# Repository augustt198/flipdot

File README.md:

# flipdot

A driver board for my 16x28 flipdot display (Luminator MAX 3000).

The `connector` folder has a PCB for converting the 3x32 connector on the display to a
2x32 connector (which is easier to find cables for).

The `driver` folder has the driver board. Ideally I would like a footprint that fits both a teensy
and an ESP2866.

### Notes

- 15V is a good voltage to flip the dots, 50mA seems like enough current.

Front:

Back:

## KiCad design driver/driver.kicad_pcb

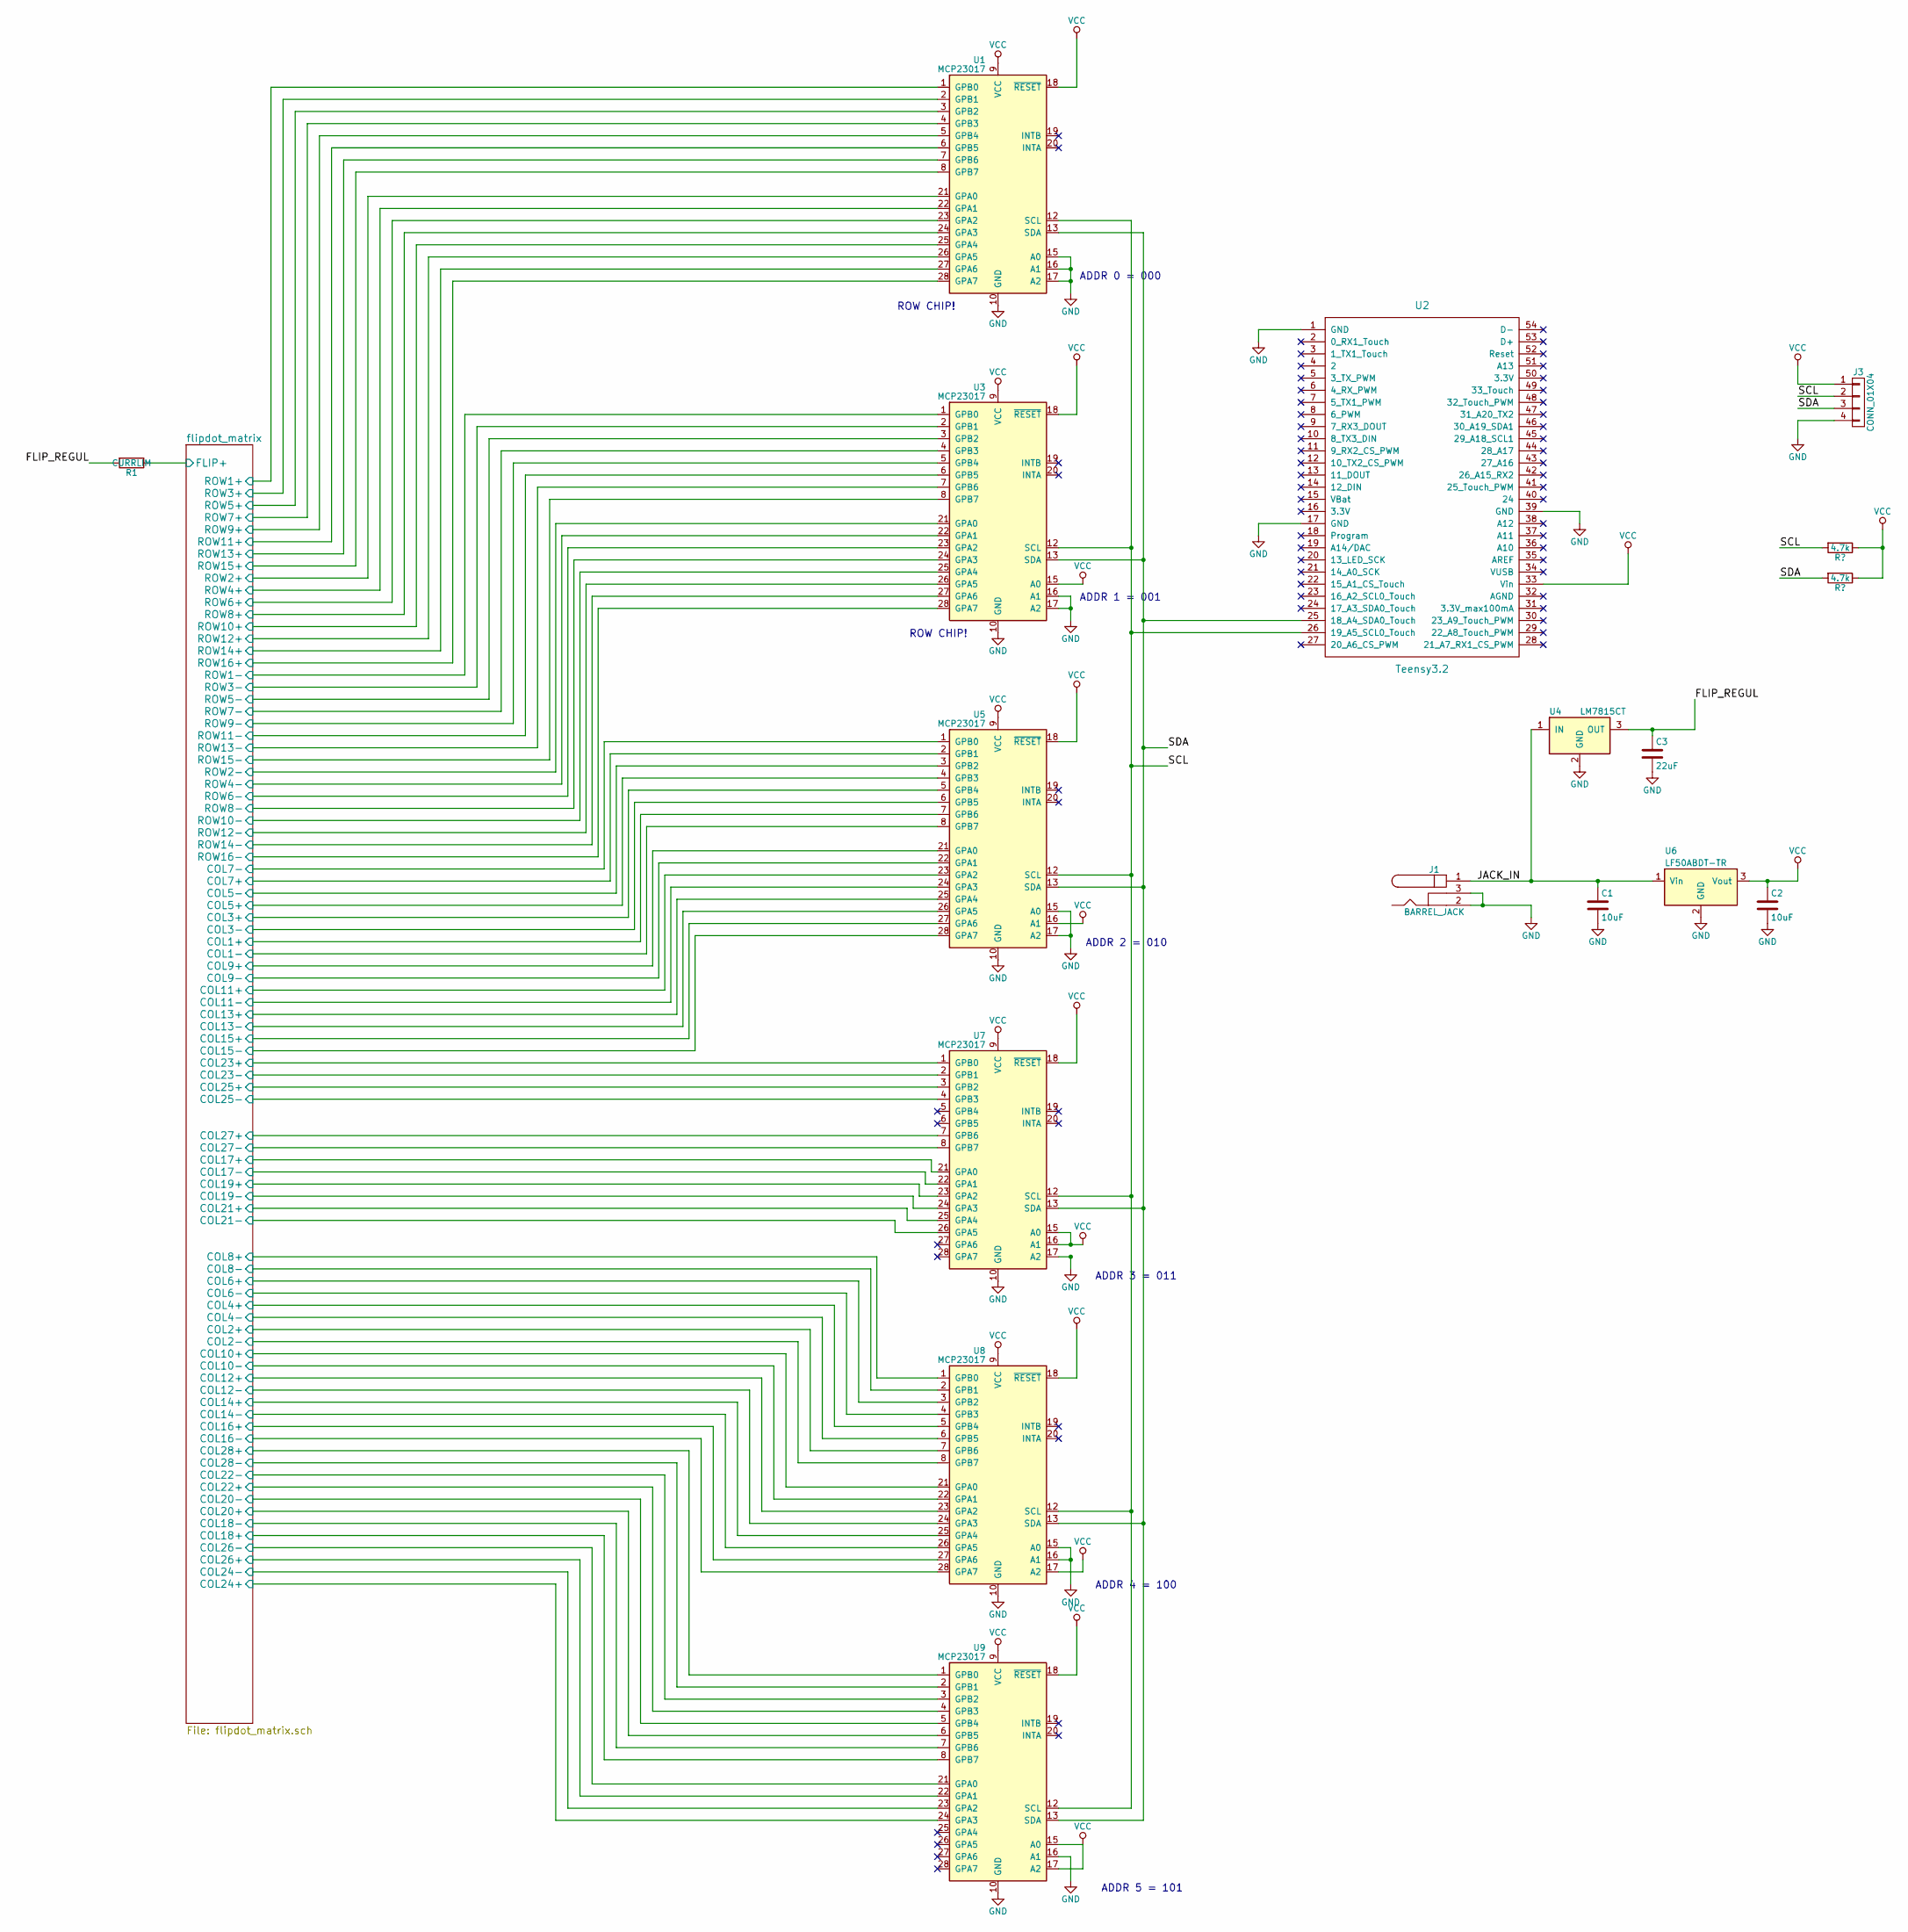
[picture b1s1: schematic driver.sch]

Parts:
C1, C2: 10uF; C_0805_HandSoldering
C3: 22uF; C_0805_HandSoldering
J1: BARREL_JACK
J3: CONN_01X04; Pin_Header_Straight_1x04_Pitch2.54mm
R1: CURRLIM; R_Axial_DIN0414_L11.9mm_D4.5mm_P15.24mm_Horizontal
U1, U3, U5, U7, U8, U9: MCP23017; SSOP-28_5.3x10.2mm_Pitch0.65mm
U2: Teensy3.2; Teensy30_31_32_LC
U4: LM7815CT; SOT-223-3Lead_TabPin2
U6: LF50ABDT-TR; SOT-223-3Lead_TabPin2

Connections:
/FLIP_REGUL: C3.1, R1.2, U4.3 (OUT)
/JACK_IN: C1.1, J1.1, U4.1 (IN), U6.1 (Vin)
/SCL: J3.2, U1.12 (SCL), U2.26 (19_A5_SCL0_Touch), U3.12 (SCL), U5.12 (SCL), U7.12 (SCL), U8.12 (SCL), U9.12 (SCL); also elsewhere on the board
/SDA: J3.3, U1.13 (SDA), U2.25 (18_A4_SDA0_Touch), U3.13 (SDA), U5.13 (SDA), U7.13 (SDA), U8.13 (SDA), U9.13 (SDA); also elsewhere on the board
/flipdot_matrix/COL1+: U5.7 (GPB6); also elsewhere on the board
/flipdot_matrix/COL1-: U5.8 (GPB7); also elsewhere on the board
/flipdot_matrix/COL2+: U8.7 (GPB6); also elsewhere on the board
/flipdot_matrix/COL2-: U8.8 (GPB7); also elsewhere on the board
/flipdot_matrix/COL3+: U5.5 (GPB4); also elsewhere on the board
/flipdot_matrix/COL3-: U5.6 (GPB5); also elsewhere on the board
/flipdot_matrix/COL4+: U8.5 (GPB4); also elsewhere on the board
/flipdot_matrix/COL4-: U8.6 (GPB5); also elsewhere on the board
/flipdot_matrix/COL5+: U5.4 (GPB3); also elsewhere on the board
/flipdot_matrix/COL5-: U5.3 (GPB2); also elsewhere on the board
/flipdot_matrix/COL6+: U8.3 (GPB2); also elsewhere on the board
/flipdot_matrix/COL6-: U8.4 (GPB3); also elsewhere on the board
/flipdot_matrix/COL7+: U5.2 (GPB1); also elsewhere on the board
/flipdot_matrix/COL7-: U5.1 (GPB0); also elsewhere on the board
/flipdot_matrix/COL8+: U8.1 (GPB0); also elsewhere on the board
/flipdot_matrix/COL8-: U8.2 (GPB1); also elsewhere on the board
/flipdot_matrix/COL9+: U5.21 (GPA0); also elsewhere on the board
/flipdot_matrix/COL9-: U5.22 (GPA1); also elsewhere on the board
/flipdot_matrix/COL10+: U8.21 (GPA0); also elsewhere on the board
/flipdot_matrix/COL10-: U8.22 (GPA1); also elsewhere on the board
/flipdot_matrix/COL11+: U5.23 (GPA2); also elsewhere on the board
/flipdot_matrix/COL11-: U5.24 (GPA3); also elsewhere on the board
/flipdot_matrix/COL12+: U8.23 (GPA2); also elsewhere on the board
/flipdot_matrix/COL12-: U8.24 (GPA3); also elsewhere on the board
/flipdot_matrix/COL13+: U5.25 (GPA4); also elsewhere on the board
/flipdot_matrix/COL13-: U5.26 (GPA5); also elsewhere on the board
/flipdot_matrix/COL14+: U8.25 (GPA4); also elsewhere on the board
/flipdot_matrix/COL14-: U8.26 (GPA5); also elsewhere on the board
/flipdot_matrix/COL15+: U5.27 (GPA6); also elsewhere on the board
/flipdot_matrix/COL15-: U5.28 (GPA7); also elsewhere on the board
/flipdot_matrix/COL16+: U8.27 (GPA6); also elsewhere on the board
/flipdot_matrix/COL16-: U8.28 (GPA7); also elsewhere on the board
/flipdot_matrix/COL17+: U7.21 (GPA0); also elsewhere on the board
/flipdot_matrix/COL17-: U7.22 (GPA1); also elsewhere on the board
/flipdot_matrix/COL18+: U9.8 (GPB7); also elsewhere on the board
/flipdot_matrix/COL18-: U9.7 (GPB6); also elsewhere on the board
/flipdot_matrix/COL19+: U7.23 (GPA2); also elsewhere on the board
/flipdot_matrix/COL19-: U7.24 (GPA3); also elsewhere on the board
/flipdot_matrix/COL20+: U9.6 (GPB5); also elsewhere on the board
/flipdot_matrix/COL20-: U9.5 (GPB4); also elsewhere on the board
/flipdot_matrix/COL21+: U7.25 (GPA4); also elsewhere on the board
/flipdot_matrix/COL21-: U7.26 (GPA5); also elsewhere on the board
/flipdot_matrix/COL22+: U9.4 (GPB3); also elsewhere on the board
/flipdot_matrix/COL22-: U9.3 (GPB2); also elsewhere on the board
/flipdot_matrix/COL23+: U7.1 (GPB0); also elsewhere on the board
/flipdot_matrix/COL23-: U7.2 (GPB1); also elsewhere on the board
/flipdot_matrix/COL24+: U9.24 (GPA3); also elsewhere on the board
/flipdot_matrix/COL24-: U9.23 (GPA2); also elsewhere on the board
/flipdot_matrix/COL25+: U7.3 (GPB2); also elsewhere on the board
/flipdot_matrix/COL25-: U7.4 (GPB3); also elsewhere on the board
/flipdot_matrix/COL26+: U9.22 (GPA1); also elsewhere on the board
/flipdot_matrix/COL26-: U9.21 (GPA0); also elsewhere on the board
/flipdot_matrix/COL27+: U7.7 (GPB6); also elsewhere on the board
/flipdot_matrix/COL27-: U7.8 (GPB7); also elsewhere on the board
/flipdot_matrix/COL28+: U9.1 (GPB0); also elsewhere on the board
/flipdot_matrix/COL28-: U9.2 (GPB1); also elsewhere on the board
/flipdot_matrix/FLIP+: R1.1; also elsewhere on the board
/flipdot_matrix/ROW1+: U1.2 (GPB1); also elsewhere on the board
/flipdot_matrix/ROW1-: U3.2 (GPB1); also elsewhere on the board
/flipdot_matrix/ROW2+: U1.22 (GPA1); also elsewhere on the board
/flipdot_matrix/ROW2-: U3.22 (GPA1); also elsewhere on the board
/flipdot_matrix/ROW3+: U1.1 (GPB0); also elsewhere on the board
/flipdot_matrix/ROW3-: U3.1 (GPB0); also elsewhere on the board
/flipdot_matrix/ROW4+: U1.21 (GPA0); also elsewhere on the board
/flipdot_matrix/ROW4-: U3.21 (GPA0); also elsewhere on the board
/flipdot_matrix/ROW5+: U1.4 (GPB3); also elsewhere on the board
/flipdot_matrix/ROW5-: U3.4 (GPB3); also elsewhere on the board
/flipdot_matrix/ROW6+: U1.24 (GPA3); also elsewhere on the board
/flipdot_matrix/ROW6-: U3.24 (GPA3); also elsewhere on the board
/flipdot_matrix/ROW7+: U1.3 (GPB2); also elsewhere on the board
/flipdot_matrix/ROW7-: U3.3 (GPB2); also elsewhere on the board
/flipdot_matrix/ROW8+: U1.23 (GPA2); also elsewhere on the board
/flipdot_matrix/ROW8-: U3.23 (GPA2); also elsewhere on the board
/flipdot_matrix/ROW9+: U1.6 (GPB5); also elsewhere on the board
/flipdot_matrix/ROW9-: U3.6 (GPB5); also elsewhere on the board
/flipdot_matrix/ROW10+: U1.26 (GPA5); also elsewhere on the board
/flipdot_matrix/ROW10-: U3.26 (GPA5); also elsewhere on the board
/flipdot_matrix/ROW11+: U1.5 (GPB4); also elsewhere on the board
/flipdot_matrix/ROW11-: U3.5 (GPB4); also elsewhere on the board
/flipdot_matrix/ROW12+: U1.25 (GPA4); also elsewhere on the board
/flipdot_matrix/ROW12-: U3.25 (GPA4); also elsewhere on the board
/flipdot_matrix/ROW13+: U1.8 (GPB7); also elsewhere on the board
/flipdot_matrix/ROW13-: U3.8 (GPB7); also elsewhere on the board
/flipdot_matrix/ROW14+: U1.28 (GPA7); also elsewhere on the board
/flipdot_matrix/ROW14-: U3.28 (GPA7); also elsewhere on the board
/flipdot_matrix/ROW15+: U1.7 (GPB6); also elsewhere on the board
/flipdot_matrix/ROW15-: U3.7 (GPB6); also elsewhere on the board
/flipdot_matrix/ROW16+: U1.27 (GPA6); also elsewhere on the board
/flipdot_matrix/ROW16-: U3.27 (GPA6); also elsewhere on the board
GND: C1.2, C2.2, C3.2, J1.2, J1.3, J3.4, U1.10 (GND), U1.15 (A0), U1.16 (A1), U1.17 (A2), U2.1 (GND), U2.17 (GND), U2.39 (GND), U3.10 (GND), U3.16 (A1), U3.17 (A2), U4.2 (GND), U5.10 (GND), U5.15 (A0), U5.17 (A2), U6.2 (GND), U7.10 (GND), U7.17 (A2), U8.10 (GND), U8.15 (A0), U8.16 (A1), U9.10 (GND), U9.16 (A1); also elsewhere on the board
VCC: C2.1, J3.1, U1.9 (VCC), U1.18 (~RESET), U2.33 (Vin), U3.9 (VCC), U3.15 (A0), U3.18 (~RESET), U5.9 (VCC), U5.16 (A1), U5.18 (~RESET), U6.3 (Vout), U7.9 (VCC), U7.15 (A0), U7.16 (A1), U7.18 (~RESET), U8.9 (VCC), U8.17 (A2), U8.18 (~RESET), U9.9 (VCC), U9.15 (A0), U9.17 (A2), U9.18 (~RESET); also elsewhere on the board

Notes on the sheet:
ADDR 0 = 000
ADDR 1 = 001
ADDR 2 = 010
ROW CHIP!
ADDR 3 = 011
ADDR 4 = 100
ADDR 5 = 101

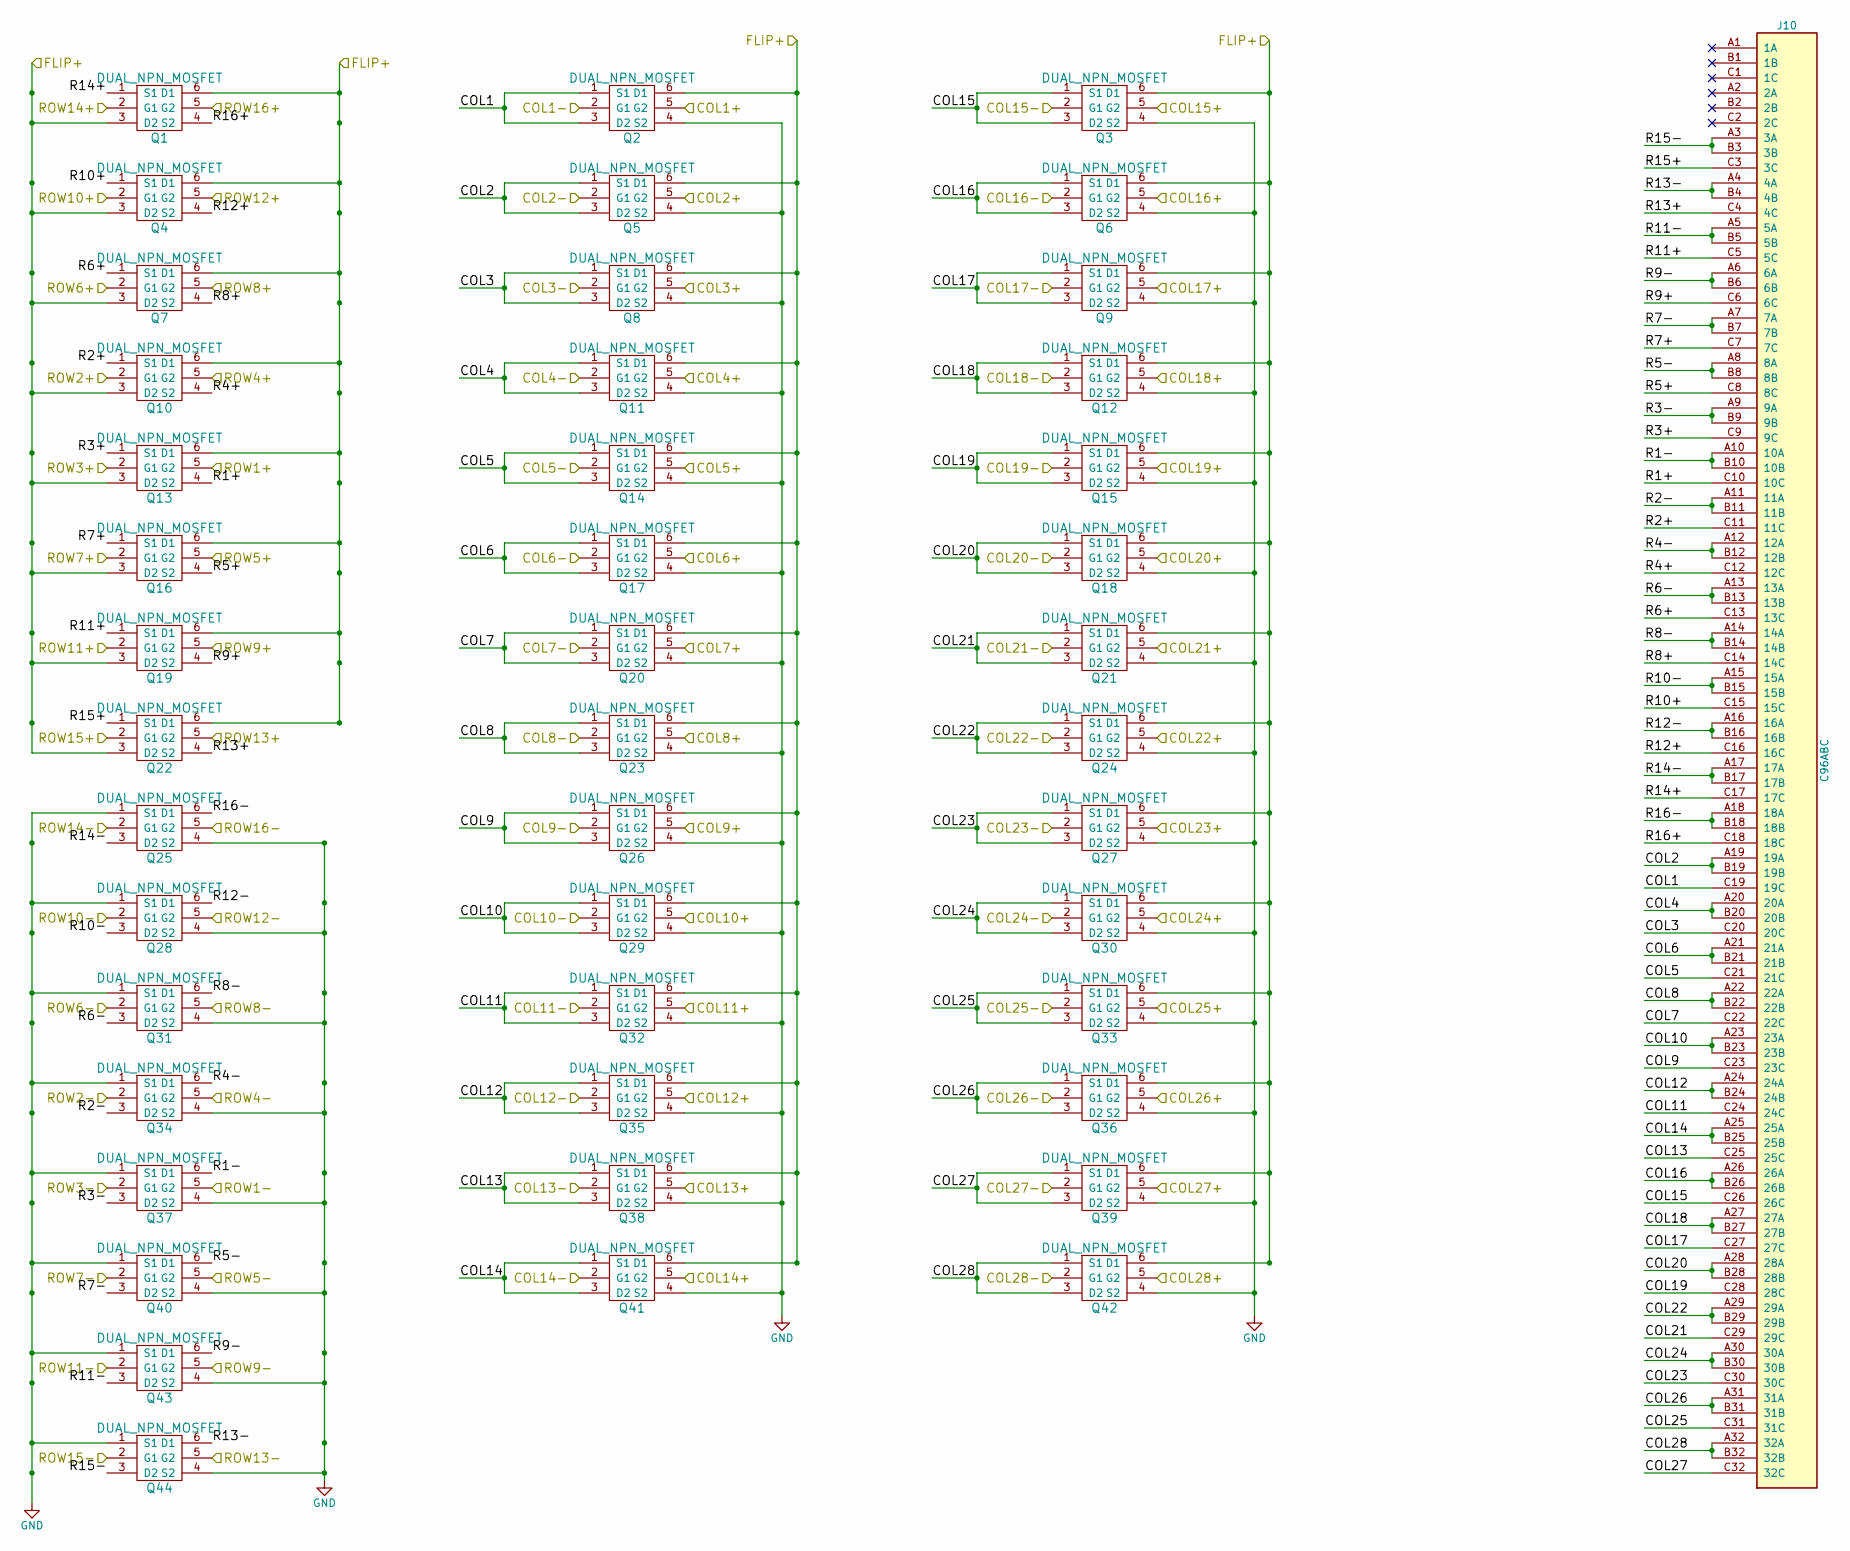
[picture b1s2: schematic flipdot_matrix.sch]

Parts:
J10: C96ABC; C96ABCMD_custom
Q1, Q2, Q3, Q4, Q5, Q6, Q7, Q8, Q9, Q10, Q11, Q12, Q13, Q14, Q15, Q16, Q17, Q18, Q19, Q20, Q21, Q22, Q23, Q24, Q25, Q26, Q27, Q28, Q29, Q30, Q31, Q32, Q33, Q34, Q35, Q36, Q37, Q38, Q39, Q40, Q41, Q42, Q43, Q44: DUAL_NPN_MOSFET; SOT-23-6_Handsoldering

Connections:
/flipdot_matrix/COL1: J10.C19 (19C), Q2.1 (S1), Q2.3 (D2)
/flipdot_matrix/COL1+: Q2.5 (G2); also elsewhere on the board
/flipdot_matrix/COL1-: Q2.2 (G1); also elsewhere on the board
/flipdot_matrix/COL2: J10.A19 (19A), J10.B19 (19B), Q5.1 (S1), Q5.3 (D2)
/flipdot_matrix/COL2+: Q5.5 (G2); also elsewhere on the board
/flipdot_matrix/COL2-: Q5.2 (G1); also elsewhere on the board
/flipdot_matrix/COL3: J10.C20 (20C), Q8.1 (S1), Q8.3 (D2)
/flipdot_matrix/COL3+: Q8.5 (G2); also elsewhere on the board
/flipdot_matrix/COL3-: Q8.2 (G1); also elsewhere on the board
/flipdot_matrix/COL4: J10.A20 (20A), J10.B20 (20B), Q11.1 (S1), Q11.3 (D2)
/flipdot_matrix/COL4+: Q11.5 (G2); also elsewhere on the board
/flipdot_matrix/COL4-: Q11.2 (G1); also elsewhere on the board
/flipdot_matrix/COL5: J10.C21 (21C), Q14.1 (S1), Q14.3 (D2)
/flipdot_matrix/COL5+: Q14.5 (G2); also elsewhere on the board
/flipdot_matrix/COL5-: Q14.2 (G1); also elsewhere on the board
/flipdot_matrix/COL6: J10.A21 (21A), J10.B21 (21B), Q17.1 (S1), Q17.3 (D2)
/flipdot_matrix/COL6+: Q17.5 (G2); also elsewhere on the board
/flipdot_matrix/COL6-: Q17.2 (G1); also elsewhere on the board
/flipdot_matrix/COL7: J10.C22 (22C), Q20.1 (S1), Q20.3 (D2)
/flipdot_matrix/COL7+: Q20.5 (G2); also elsewhere on the board
/flipdot_matrix/COL7-: Q20.2 (G1); also elsewhere on the board
/flipdot_matrix/COL8: J10.A22 (22A), J10.B22 (22B), Q23.1 (S1), Q23.3 (D2)
/flipdot_matrix/COL8+: Q23.5 (G2); also elsewhere on the board
/flipdot_matrix/COL8-: Q23.2 (G1); also elsewhere on the board
/flipdot_matrix/COL9: J10.C23 (23C), Q26.1 (S1), Q26.3 (D2)
/flipdot_matrix/COL9+: Q26.5 (G2); also elsewhere on the board
/flipdot_matrix/COL9-: Q26.2 (G1); also elsewhere on the board
/flipdot_matrix/COL10: J10.A23 (23A), J10.B23 (23B), Q29.1 (S1), Q29.3 (D2)
/flipdot_matrix/COL10+: Q29.5 (G2); also elsewhere on the board
/flipdot_matrix/COL10-: Q29.2 (G1); also elsewhere on the board
/flipdot_matrix/COL11: J10.C24 (24C), Q32.1 (S1), Q32.3 (D2)
/flipdot_matrix/COL11+: Q32.5 (G2); also elsewhere on the board
/flipdot_matrix/COL11-: Q32.2 (G1); also elsewhere on the board
/flipdot_matrix/COL12: J10.A24 (24A), J10.B24 (24B), Q35.1 (S1), Q35.3 (D2)
/flipdot_matrix/COL12+: Q35.5 (G2); also elsewhere on the board
/flipdot_matrix/COL12-: Q35.2 (G1); also elsewhere on the board
/flipdot_matrix/COL13: J10.C25 (25C), Q38.1 (S1), Q38.3 (D2)
/flipdot_matrix/COL13+: Q38.5 (G2); also elsewhere on the board
/flipdot_matrix/COL13-: Q38.2 (G1); also elsewhere on the board
/flipdot_matrix/COL14: J10.A25 (25A), J10.B25 (25B), Q41.1 (S1), Q41.3 (D2)
/flipdot_matrix/COL14+: Q41.5 (G2); also elsewhere on the board
/flipdot_matrix/COL14-: Q41.2 (G1); also elsewhere on the board
/flipdot_matrix/COL15: J10.C26 (26C), Q3.1 (S1), Q3.3 (D2)
/flipdot_matrix/COL15+: Q3.5 (G2); also elsewhere on the board
/flipdot_matrix/COL15-: Q3.2 (G1); also elsewhere on the board
/flipdot_matrix/COL16: J10.A26 (26A), J10.B26 (26B), Q6.1 (S1), Q6.3 (D2)
/flipdot_matrix/COL16+: Q6.5 (G2); also elsewhere on the board
/flipdot_matrix/COL16-: Q6.2 (G1); also elsewhere on the board
/flipdot_matrix/COL17: J10.C27 (27C), Q9.1 (S1), Q9.3 (D2)
/flipdot_matrix/COL17+: Q9.5 (G2); also elsewhere on the board
/flipdot_matrix/COL17-: Q9.2 (G1); also elsewhere on the board
/flipdot_matrix/COL18: J10.A27 (27A), J10.B27 (27B), Q12.1 (S1), Q12.3 (D2)
/flipdot_matrix/COL18+: Q12.5 (G2); also elsewhere on the board
/flipdot_matrix/COL18-: Q12.2 (G1); also elsewhere on the board
/flipdot_matrix/COL19: J10.C28 (28C), Q15.1 (S1), Q15.3 (D2)
/flipdot_matrix/COL19+: Q15.5 (G2); also elsewhere on the board
/flipdot_matrix/COL19-: Q15.2 (G1); also elsewhere on the board
/flipdot_matrix/COL20: J10.A28 (28A), J10.B28 (28B), Q18.1 (S1), Q18.3 (D2)
/flipdot_matrix/COL20+: Q18.5 (G2); also elsewhere on the board
/flipdot_matrix/COL20-: Q18.2 (G1); also elsewhere on the board
/flipdot_matrix/COL21: J10.C29 (29C), Q21.1 (S1), Q21.3 (D2)
/flipdot_matrix/COL21+: Q21.5 (G2); also elsewhere on the board
/flipdot_matrix/COL21-: Q21.2 (G1); also elsewhere on the board
/flipdot_matrix/COL22: J10.A29 (29A), J10.B29 (29B), Q24.1 (S1), Q24.3 (D2)
/flipdot_matrix/COL22+: Q24.5 (G2); also elsewhere on the board
/flipdot_matrix/COL22-: Q24.2 (G1); also elsewhere on the board
/flipdot_matrix/COL23: J10.C30 (30C), Q27.1 (S1), Q27.3 (D2)
/flipdot_matrix/COL23+: Q27.5 (G2); also elsewhere on the board
/flipdot_matrix/COL23-: Q27.2 (G1); also elsewhere on the board
/flipdot_matrix/COL24: J10.A30 (30A), J10.B30 (30B), Q30.1 (S1), Q30.3 (D2)
/flipdot_matrix/COL24+: Q30.5 (G2); also elsewhere on the board
/flipdot_matrix/COL24-: Q30.2 (G1); also elsewhere on the board
/flipdot_matrix/COL25: J10.C31 (31C), Q33.1 (S1), Q33.3 (D2)
/flipdot_matrix/COL25+: Q33.5 (G2); also elsewhere on the board
/flipdot_matrix/COL25-: Q33.2 (G1); also elsewhere on the board
/flipdot_matrix/COL26: J10.A31 (31A), J10.B31 (31B), Q36.1 (S1), Q36.3 (D2)
/flipdot_matrix/COL26+: Q36.5 (G2); also elsewhere on the board
/flipdot_matrix/COL26-: Q36.2 (G1); also elsewhere on the board
/flipdot_matrix/COL27: J10.C32 (32C), Q39.1 (S1), Q39.3 (D2)
/flipdot_matrix/COL27+: Q39.5 (G2); also elsewhere on the board
/flipdot_matrix/COL27-: Q39.2 (G1); also elsewhere on the board
/flipdot_matrix/COL28: J10.A32 (32A), J10.B32 (32B), Q42.1 (S1), Q42.3 (D2)
/flipdot_matrix/COL28+: Q42.5 (G2); also elsewhere on the board
/flipdot_matrix/COL28-: Q42.2 (G1); also elsewhere on the board
/flipdot_matrix/FLIP+: Q1.3 (D2), Q1.6 (D1), Q2.6 (D1), Q3.6 (D1), Q4.3 (D2), Q4.6 (D1), Q5.6 (D1), Q6.6 (D1), Q7.3 (D2), Q7.6 (D1), Q8.6 (D1), Q9.6 (D1), Q10.3 (D2), Q10.6 (D1), Q11.6 (D1), Q12.6 (D1), Q13.3 (D2), Q13.6 (D1), Q14.6 (D1), Q15.6 (D1), Q16.3 (D2), Q16.6 (D1), Q17.6 (D1), Q18.6 (D1), Q19.3 (D2), Q19.6 (D1), Q20.6 (D1), Q21.6 (D1), Q22.3 (D2), Q22.6 (D1), Q23.6 (D1), Q24.6 (D1), Q26.6 (D1), Q27.6 (D1), Q29.6 (D1), Q30.6 (D1), Q32.6 (D1), Q33.6 (D1), Q35.6 (D1), Q36.6 (D1), Q38.6 (D1), Q39.6 (D1), Q41.6 (D1), Q42.6 (D1); also elsewhere on the board
/flipdot_matrix/R1+: J10.C10 (10C), Q13.4 (S2)
/flipdot_matrix/R1-: J10.A10 (10A), J10.B10 (10B), Q37.6 (D1)
/flipdot_matrix/R2+: J10.C11 (11C), Q10.1 (S1)
/flipdot_matrix/R2-: J10.A11 (11A), J10.B11 (11B), Q34.3 (D2)
/flipdot_matrix/R3+: J10.C9 (9C), Q13.1 (S1)
/flipdot_matrix/R3-: J10.A9 (9A), J10.B9 (9B), Q37.3 (D2)
/flipdot_matrix/R4+: J10.C12 (12C), Q10.4 (S2)
/flipdot_matrix/R4-: J10.A12 (12A), J10.B12 (12B), Q34.6 (D1)
/flipdot_matrix/R5+: J10.C8 (8C), Q16.4 (S2)
/flipdot_matrix/R5-: J10.A8 (8A), J10.B8 (8B), Q40.6 (D1)
/flipdot_matrix/R6+: J10.C13 (13C), Q7.1 (S1)
/flipdot_matrix/R6-: J10.A13 (13A), J10.B13 (13B), Q31.3 (D2)
/flipdot_matrix/R7+: J10.C7 (7C), Q16.1 (S1)
/flipdot_matrix/R7-: J10.A7 (7A), J10.B7 (7B), Q40.3 (D2)
/flipdot_matrix/R8+: J10.C14 (14C), Q7.4 (S2)
/flipdot_matrix/R8-: J10.A14 (14A), J10.B14 (14B), Q31.6 (D1)
/flipdot_matrix/R9+: J10.C6 (6C), Q19.4 (S2)
/flipdot_matrix/R9-: J10.A6 (6A), J10.B6 (6B), Q43.6 (D1)
/flipdot_matrix/R10+: J10.C15 (15C), Q4.1 (S1)
/flipdot_matrix/R10-: J10.A15 (15A), J10.B15 (15B), Q28.3 (D2)
/flipdot_matrix/R11+: J10.C5 (5C), Q19.1 (S1)
/flipdot_matrix/R11-: J10.A5 (5A), J10.B5 (5B), Q43.3 (D2)
/flipdot_matrix/R12+: J10.C16 (16C), Q4.4 (S2)
/flipdot_matrix/R12-: J10.A16 (16A), J10.B16 (16B), Q28.6 (D1)
/flipdot_matrix/R13+: J10.C4 (4C), Q22.4 (S2)
/flipdot_matrix/R13-: J10.A4 (4A), J10.B4 (4B), Q44.6 (D1)
/flipdot_matrix/R14+: J10.C17 (17C), Q1.1 (S1)
/flipdot_matrix/R14-: J10.A17 (17A), J10.B17 (17B), Q25.3 (D2)
/flipdot_matrix/R15+: J10.C3 (3C), Q22.1 (S1)
/flipdot_matrix/R15-: J10.A3 (3A), J10.B3 (3B), Q44.3 (D2)
/flipdot_matrix/R16+: J10.C18 (18C), Q1.4 (S2)
/flipdot_matrix/R16-: J10.A18 (18A), J10.B18 (18B), Q25.6 (D1)
/flipdot_matrix/ROW1+: Q13.5 (G2); also elsewhere on the board
/flipdot_matrix/ROW1-: Q37.5 (G2); also elsewhere on the board
/flipdot_matrix/ROW2+: Q10.2 (G1); also elsewhere on the board
/flipdot_matrix/ROW2-: Q34.2 (G1); also elsewhere on the board
/flipdot_matrix/ROW3+: Q13.2 (G1); also elsewhere on the board
/flipdot_matrix/ROW3-: Q37.2 (G1); also elsewhere on the board
/flipdot_matrix/ROW4+: Q10.5 (G2); also elsewhere on the board
/flipdot_matrix/ROW4-: Q34.5 (G2); also elsewhere on the board
/flipdot_matrix/ROW5+: Q16.5 (G2); also elsewhere on the board
/flipdot_matrix/ROW5-: Q40.5 (G2); also elsewhere on the board
/flipdot_matrix/ROW6+: Q7.2 (G1); also elsewhere on the board
/flipdot_matrix/ROW6-: Q31.2 (G1); also elsewhere on the board
/flipdot_matrix/ROW7+: Q16.2 (G1); also elsewhere on the board
/flipdot_matrix/ROW7-: Q40.2 (G1); also elsewhere on the board
/flipdot_matrix/ROW8+: Q7.5 (G2); also elsewhere on the board
/flipdot_matrix/ROW8-: Q31.5 (G2); also elsewhere on the board
/flipdot_matrix/ROW9+: Q19.5 (G2); also elsewhere on the board
/flipdot_matrix/ROW9-: Q43.5 (G2); also elsewhere on the board
/flipdot_matrix/ROW10+: Q4.2 (G1); also elsewhere on the board
/flipdot_matrix/ROW10-: Q28.2 (G1); also elsewhere on the board
/flipdot_matrix/ROW11+: Q19.2 (G1); also elsewhere on the board
/flipdot_matrix/ROW11-: Q43.2 (G1); also elsewhere on the board
/flipdot_matrix/ROW12+: Q4.5 (G2); also elsewhere on the board
/flipdot_matrix/ROW12-: Q28.5 (G2); also elsewhere on the board
/flipdot_matrix/ROW13+: Q22.5 (G2); also elsewhere on the board
/flipdot_matrix/ROW13-: Q44.5 (G2); also elsewhere on the board
/flipdot_matrix/ROW14+: Q1.2 (G1); also elsewhere on the board
/flipdot_matrix/ROW14-: Q25.2 (G1); also elsewhere on the board
/flipdot_matrix/ROW15+: Q22.2 (G1); also elsewhere on the board
/flipdot_matrix/ROW15-: Q44.2 (G1); also elsewhere on the board
/flipdot_matrix/ROW16+: Q1.5 (G2); also elsewhere on the board
/flipdot_matrix/ROW16-: Q25.5 (G2); also elsewhere on the board
GND: Q2.4 (S2), Q3.4 (S2), Q5.4 (S2), Q6.4 (S2), Q8.4 (S2), Q9.4 (S2), Q11.4 (S2), Q12.4 (S2), Q14.4 (S2), Q15.4 (S2), Q17.4 (S2), Q18.4 (S2), Q20.4 (S2), Q21.4 (S2), Q23.4 (S2), Q24.4 (S2), Q25.1 (S1), Q25.4 (S2), Q26.4 (S2), Q27.4 (S2), Q28.1 (S1), Q28.4 (S2), Q29.4 (S2), Q30.4 (S2), Q31.1 (S1), Q31.4 (S2), Q32.4 (S2), Q33.4 (S2), Q34.1 (S1), Q34.4 (S2), Q35.4 (S2), Q36.4 (S2), Q37.1 (S1), Q37.4 (S2), Q38.4 (S2), Q39.4 (S2), Q40.1 (S1), Q40.4 (S2), Q41.4 (S2), Q42.4 (S2), Q43.1 (S1), Q43.4 (S2), Q44.1 (S1), Q44.4 (S2); also elsewhere on the board

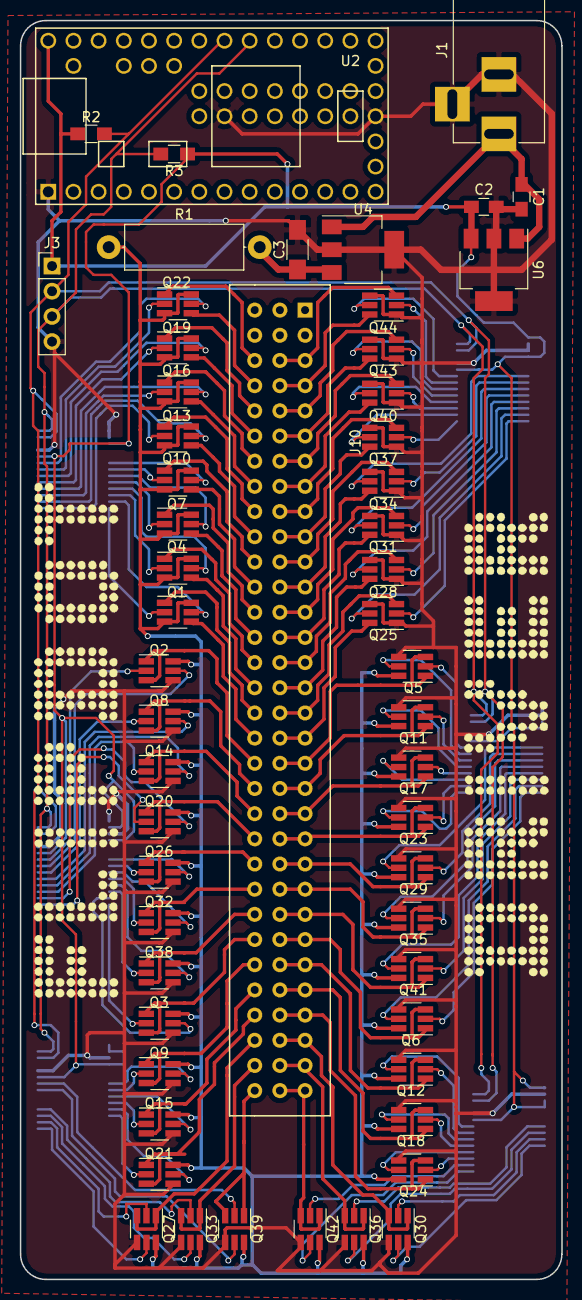
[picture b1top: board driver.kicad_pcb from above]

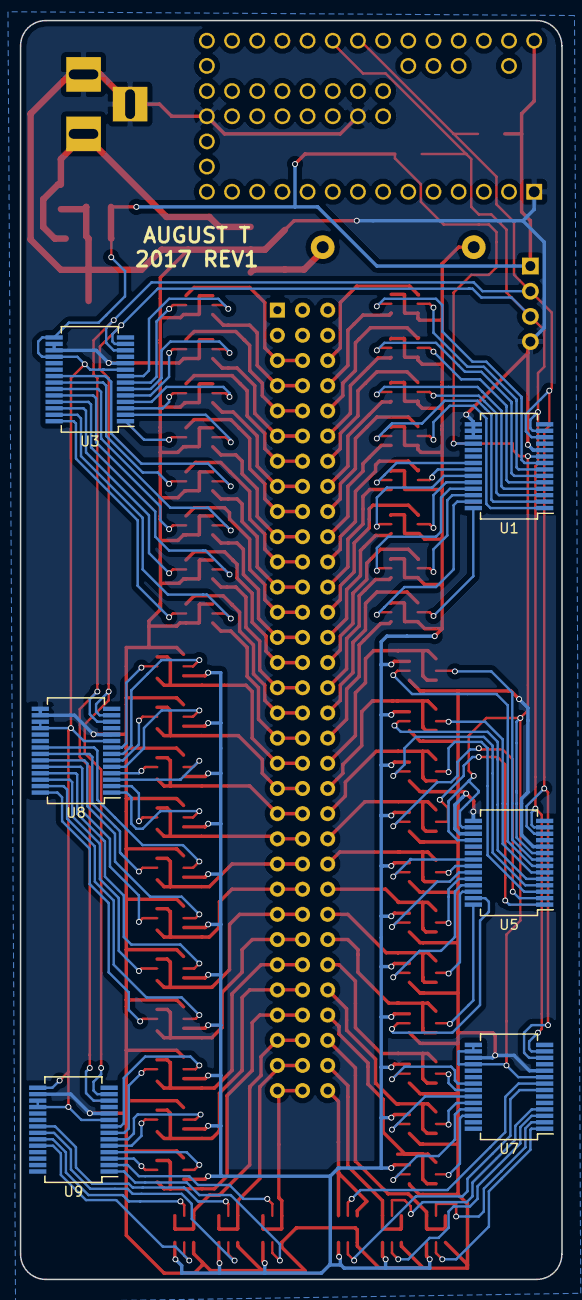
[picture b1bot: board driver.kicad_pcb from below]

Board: 2 copper layers, 54.6 x 127.0 mm, 62 parts (6 on the bottom side), 155 nets.

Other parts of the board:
R2, R3: 4.7k; R_0805_HandSoldering

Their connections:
/SCL: R2.2; also elsewhere on the board
/SDA: R3.2; also elsewhere on the board
VCC: R2.1, R3.1; also elsewhere on the board

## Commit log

2017-08-19 layout 2nd transistor array
2017-08-30 Better row pins
2017-08-30 nooooooo
    component pin numbers didn't match footprint
2017-09-10 lots of revs
2017-09-10 more work
2017-09-16 closer to final
2017-09-18 wild changes
2017-09-24 done??
    probably not
2017-09-25 fix major goof
2017-09-25 generate gerbers
2017-09-25 Add images to readme
